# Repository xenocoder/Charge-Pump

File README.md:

# Charge-Pump
9V -> 18v charge pump

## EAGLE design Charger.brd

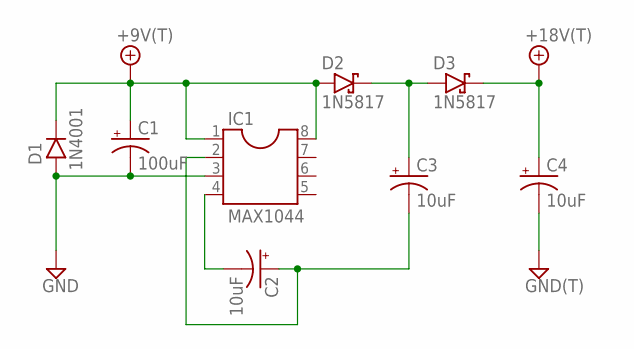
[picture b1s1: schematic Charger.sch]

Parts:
+9V: +9V(T); SQUARE
+18V: +18V(T); SQUARE
C1: 100uF; 080_035_1
C2, C3, C4: 10uF; 050_020_1
D1: 1N4001; DO41-3
D2, D3: 1N5817; DO41-3
GND: GND(T); SQUARE
IC1: MAX1044; DIL08

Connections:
+9V: +9V.1, C1.+, D1.C, D2.A, IC1.1, IC1.8
+18V: +18V.1, C4.+, D3.C
GND: C1.-, C4.-, D1.A, GND.1, IC1.3
unnamed: C2.-, IC1.4
unnamed: C2.+, C3.-, IC1.2
unnamed: C3.+, D2.C, D3.A

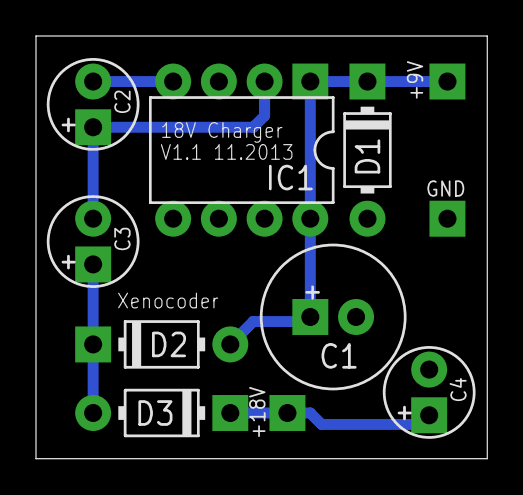
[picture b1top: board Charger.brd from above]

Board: 2 copper layers, 25.1 x 23.5 mm, 11 parts (0 on the bottom side), 6 nets.

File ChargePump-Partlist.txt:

Partlist

Exported from Charger.sch at 11/20/2013 9:33:02 PM

EAGLE Version 6.2.0 Copyright (c) 1988-2012 CadSoft

Assembly variant: 

Part     Value          Device     Package   Library             Sheet

+9V      +9V(T)         +9V(T)     SQUARE    gm-supply           1
+18V     +18V(T)        +18V(T)    SQUARE    gm-supply           1
C1       100uF          0801       080_035_1 gm-caps-electro-pol 1
C2       10uF           0501       050_020_1 gm-caps-electro-pol 1
C3       10uF           0501       050_020_1 gm-caps-electro-pol 1
C4       10uF           0501       050_020_1 gm-caps-electro-pol 1
D1       1N4001         1N400X.3   DO41-3    gm-diodes           1
D2       1N5817         1N5817     DO41-3    gm-diodes           1
D3       1N5817         1N5817     DO41-3    gm-diodes           1
GND      GND(T)         GND(T)     SQUARE    gm-supply           1
IC1      MAX1044        MAX1044    DIL08     gm-ics              1

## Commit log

2015-10-08 First upload of files to make V1.0
2015-10-08 Changes in schematic and board to v1.1
